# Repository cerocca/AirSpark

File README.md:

# AirSpark
Spark core powered Weather & Air Monitoring Device

Weather sensors:
- DHT22
- BMP180
- RJ sockets for external rain and wind meters

Air quality sensors:
- MICS-4514
- TGS-2xxx socket (fits TGS-2600, TGS-2602, etc)
- MQ-x socket (fits MQ-3, MQ-5, etc)

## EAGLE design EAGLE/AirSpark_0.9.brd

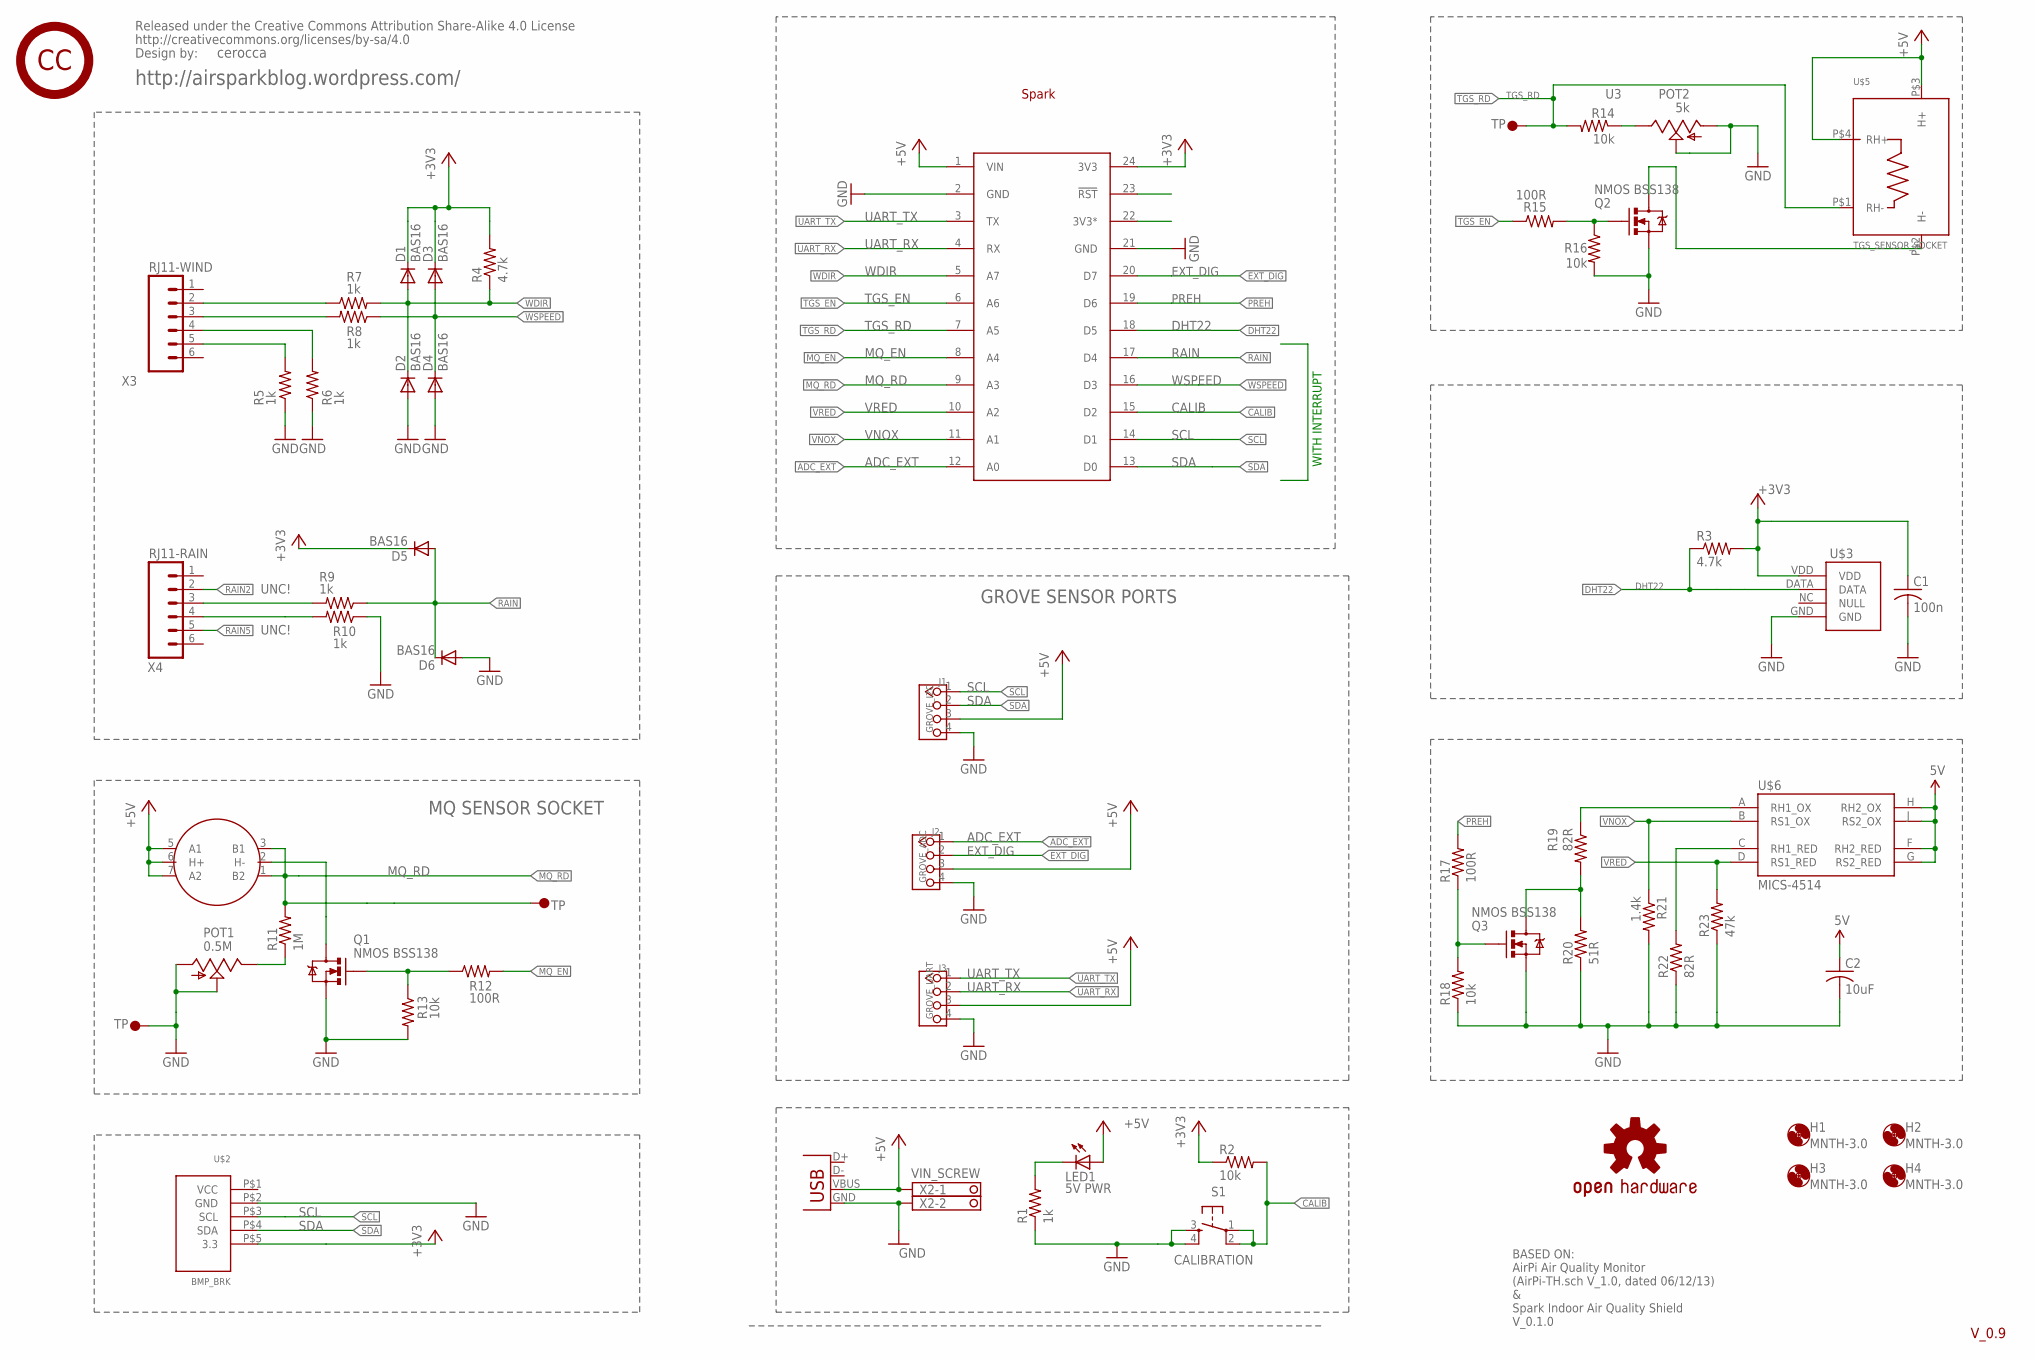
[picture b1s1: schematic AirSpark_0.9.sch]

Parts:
C1: 100n; C0603
C2: 10uF; C0603
D1, D2, D3, D4, D5, D6: BAS16; SOD-323
H1, H2, H3, H4: MNTH-3.0; 3,0
J1: GROVE_I2C; 4P-2.0
J2: GROVE_ADC; 4P-2.0
J3: GROVE_UART; 4P-2.0
LED1: 5V PWR; LED3MM
LOGO101: OSHW-LOGOL; OSHW-LOGO-L
POT1: 0.5M; B25P
POT2: 5k; B25P
Q1, Q2, Q3: NMOS BSS138; SOT23-3
R1, R5, R6, R7, R8, R9, R10: 1k; R0603
R2, R13, R14, R16, R18: 10k; R0603
R3, R4: 4.7k; R0603
R11: 1M; R0603
R12, R15, R17: 100R; R0603
R19, R22: 82R; R0603
R20: 51R; R0603
R21: 1.4k; R0603
R23: 47k; R0603
S1: CALIBRATION; TACTILE-PTH
U$1: SPARK_CORECORE; SPARK_CORE
U$2: BMP_BRK
U$3: DHT22
U$4: MQ_SENSOR_SOCKET
U$5: TGS_SENSOR_SOCKET; SR6
U$6: MICS-4514; MICS_10-SMD
U$7: MQ_TP; TESTPAD-PTR
U$8: TGS_TP; TESTPAD-PTR
U$9: GND_TP; TESTPAD-PTR
U$101: CC
U$102: CREATIVE_COMMONS
U$103: SPARK_LOGO..; SPARK_LOGO
X1: USB-SMD-NS; USB-MINIB-NOSTOP
X2: VIN_SCREW; 1751248
X3: RJ11-WIND; RJ11-6
X4: RJ11-RAIN; RJ11-6

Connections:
+3V3: C1.1, D1.1 (C), D3.1 (C), D5.1 (C), R2.1, R3.2, R4.2, U$1.24 (3V3), U$2.P$5 (3.3), U$3.VDD
+5V: C2.1, J1.3, J2.3, J3.3, LED1.A, U$1.1 (VIN), U$4.5 (A1), U$4.6 (H+), U$4.7 (A2), U$5.P$3 (H+), U$5.P$4 (RH+), U$6.F (RH2_RED), U$6.G (RS2_RED), U$6.H (RH2_OX), U$6.J (RS2_OX), X1.VBUS, X2.1
ADC_EXT: J2.1, U$1.12 (A0)
CALIB: R2.2, S1.1, S1.2, U$1.15 (D2)
DHT22: R3.1, U$1.18 (D5), U$3.DATA
EXT_DIG: J2.2, U$1.20 (D7)
GND: C1.2, C2.2, D2.2 (A), D4.2 (A), D6.2 (A), J1.4, J2.4, J3.4, POT1.A, POT1.S, POT2.A, POT2.S, Q1.2 (S), Q2.2 (S), Q3.2 (S), R1.1, R5.1, R6.1, R10.1, R13.2, R16.2, R18.1, R20.1, R21.2, R22.1, R23.1, S1.3, S1.4, U$1.2 (GND), U$1.21 (GND), U$2.P$2 (GND), U$3.GND, U$9.TP, X1.GND, X2.2
MQ_EN: R12.2, U$1.8 (A4)
MQ_RD: R11.2, U$1.9 (A3), U$4.1 (B2), U$4.3 (B1), U$7.TP
unnamed: R19.1, U$6.A (RH1_OX)
unnamed: POT2.E, R14.1
unnamed: Q3.1 (G), R17.1, R18.2
unnamed: R22.2, U$6.C (RH1_RED)
unnamed: Q3.3 (D), R19.2, R20.2
unnamed: Q1.3 (D), U$4.2 (H-)
unnamed: Q2.3 (D), U$5.P$2 (H-)
unnamed: Q1.1 (G), R12.1, R13.1
unnamed: LED1.K (C), R1.2
unnamed: Q2.1 (G), R15.2, R16.1
unnamed: POT1.E, R11.1
unnamed: R7.1, X3.2
unnamed: R8.2, X3.3
unnamed: R9.2, X4.3
unnamed: R10.2, X4.4
unnamed: R5.2, X3.5
unnamed: R6.2, X3.4
PREH: R17.2, U$1.19 (D6)
RAIN: D5.2 (A), D6.1 (C), R9.1, U$1.17 (D4)
RAIN2: X4.2
RAIN5: X4.5
SCL: J1.1, U$1.14 (D1), U$2.P$3 (SCL)
SDA: J1.2, U$1.13 (D0), U$2.P$4 (SDA)
TGS_EN: R15.1, U$1.6 (A6)
TGS_RD: R14.2, U$1.7 (A5), U$5.P$1 (RH-), U$8.TP
UART_RX: J3.2, U$1.4 (RX)
UART_TX: J3.1, U$1.3 (TX)
VNOX: R21.1, U$1.11 (A1), U$6.B (RS1_OX)
VRED: R23.2, U$1.10 (A2), U$6.D (RS1_RED)
WDIR: D1.2 (A), D2.1 (C), R4.1, R7.2, U$1.5 (A7)
WSPEED: D3.2 (A), D4.1 (C), R8.1, U$1.16 (D3)

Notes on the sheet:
BASED ON: AirPi Air Quality Monitor (AirPi-TH.sch V_1.0, dated 06/12/13) & Spark Indoor Air Quality Shield V_0.1.0
U$3
GROVE SENSOR PORTS
MQ SENSOR SOCKET
UNC!
WITH INTERRUPT
http://airsparkblog.wordpress.com/
cerocca
V_0.9

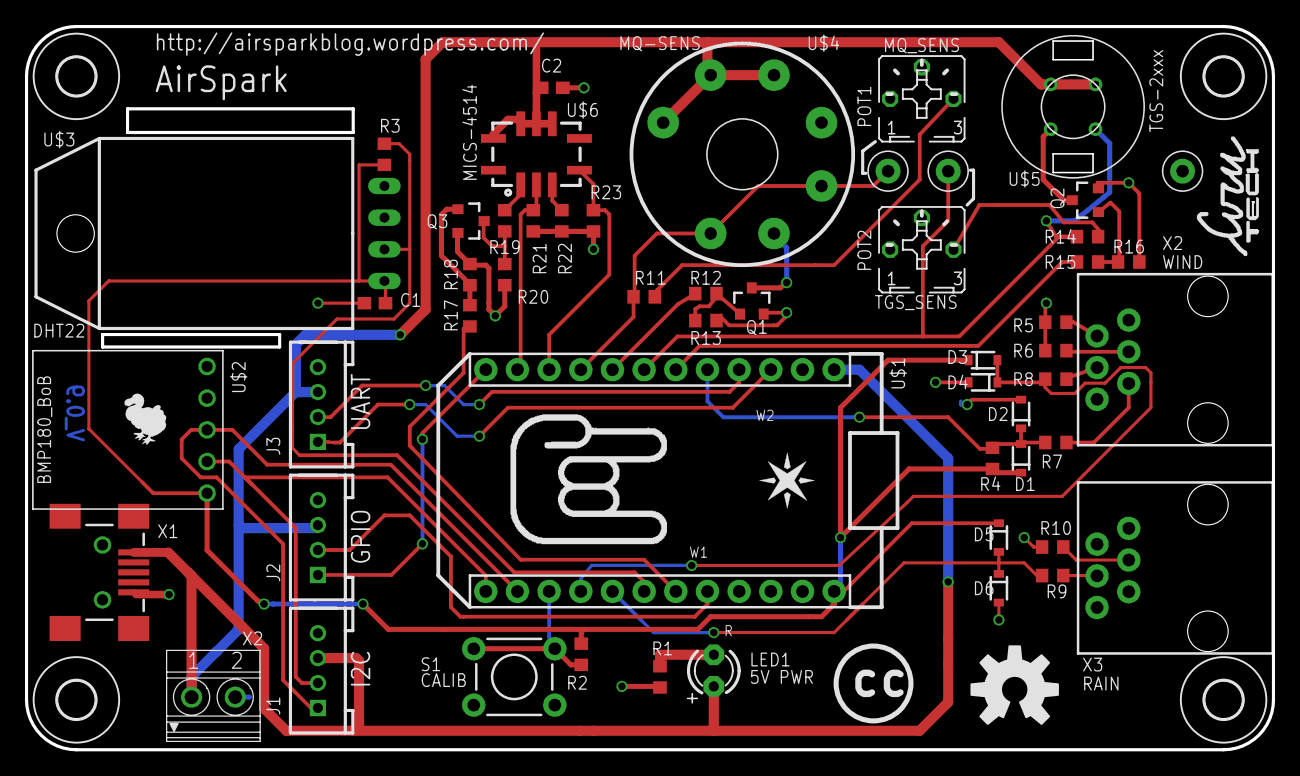
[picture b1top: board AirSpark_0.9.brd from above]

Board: 2 copper layers, 100.0 x 58.0 mm, 65 parts (0 on the bottom side), 38 nets.

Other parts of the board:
U$12: DOD
U$104: CIRU_1X05
U$105: ROCKIT

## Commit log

2015-03-29 Main Commit
    First (main) commit with:
    - EAGLE files (schematic, layout and library)
    - Gerber Files (for Seeedstudio Fusion service)
    - BOM in excel format

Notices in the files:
parts and their libraries:
AirSpark: Released under the Creative Commons Attribution Share-Alike 4.0 License
AirSpark: http://creativecommons.org/licenses/by-sa/4.0
